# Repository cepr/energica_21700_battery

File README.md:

# energica_21700_battery
Replacement battery modules for a 2018 Energica Ego battery based on 21700 cells.

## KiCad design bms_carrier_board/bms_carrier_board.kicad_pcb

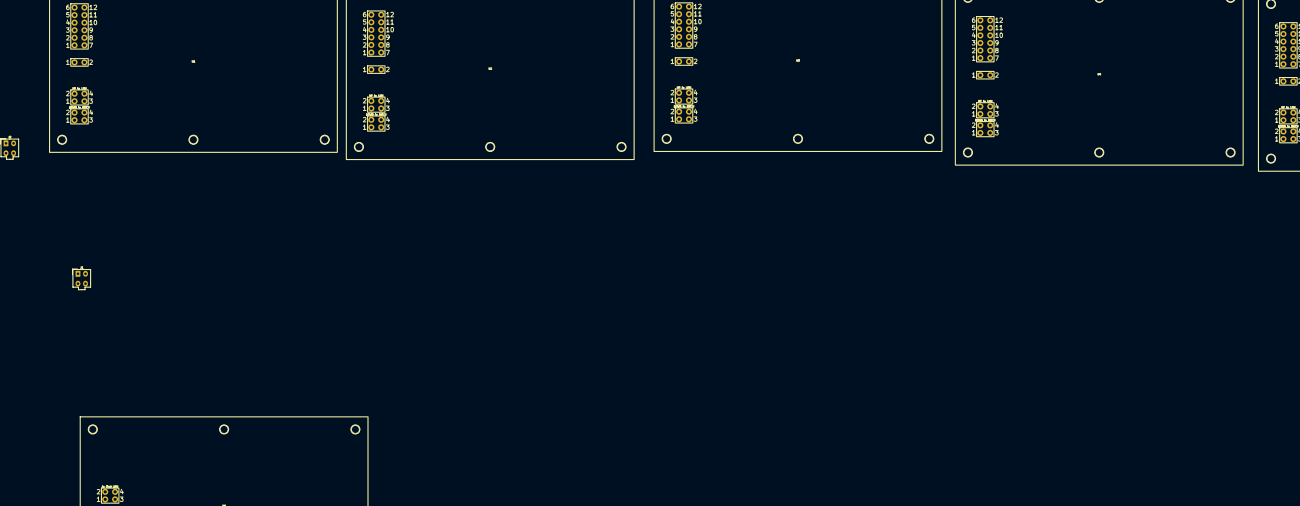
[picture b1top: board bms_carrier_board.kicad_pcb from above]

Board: 2 copper layers, 8 parts (0 on the bottom side), 18 nets, no tracks yet.

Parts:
J1, J2: Conn_02x02_Odd_Even; Molex_Mini-Fit_Jr_5566-04A_2x02_P4.20mm_Vertical
U1, U2, U3, U4, U5: LMU
U6: BMCU

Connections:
+12V: J1.2, J2.2, U1.22 (12V), U1.32 (12V), U2.22 (12V), U2.32 (12V), U3.22 (12V), U3.32 (12V), U4.22 (12V), U4.32 (12V), U5.22 (12V), U5.32 (12V)
GND: J1.1, J2.1, U1.21 (GND), U1.31 (GND), U2.21 (GND), U2.31 (GND), U3.21 (GND), U3.31 (GND), U4.21 (GND), U4.31 (GND), U5.21 (GND), U5.31 (GND)
unnamed: J1.3, U5.33 (RS485A)
unnamed: J1.4, U5.34 (RS485B)
unnamed: J2.3, U1.23 (RS485A)
unnamed: J2.4, U1.24 (RS485B)
unnamed: U1.5 (CELL8+), U2.1 (CELL1-)
unnamed: U2.5 (CELL8+), U3.1 (CELL1-)
unnamed: U3.5 (CELL8+), U4.1 (CELL1-)
unnamed: U4.5 (CELL8+), U5.1 (CELL1-)
unnamed: U1.33 (RS485A), U2.23 (RS485A)
unnamed: U1.34 (RS485B), U2.24 (RS485B)
unnamed: U2.33 (RS485A), U3.23 (RS485A)
unnamed: U2.34 (RS485B), U3.24 (RS485B)
unnamed: U3.33 (RS485A), U4.23 (RS485A)
unnamed: U3.34 (RS485B), U4.24 (RS485B)
unnamed: U4.33 (RS485A), U5.23 (RS485A)
unnamed: U4.34 (RS485B), U5.24 (RS485B)
